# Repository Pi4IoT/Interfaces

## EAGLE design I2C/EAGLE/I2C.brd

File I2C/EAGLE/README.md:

<h3>EAGLE: Schematic & Board Layout</h3>

</br>

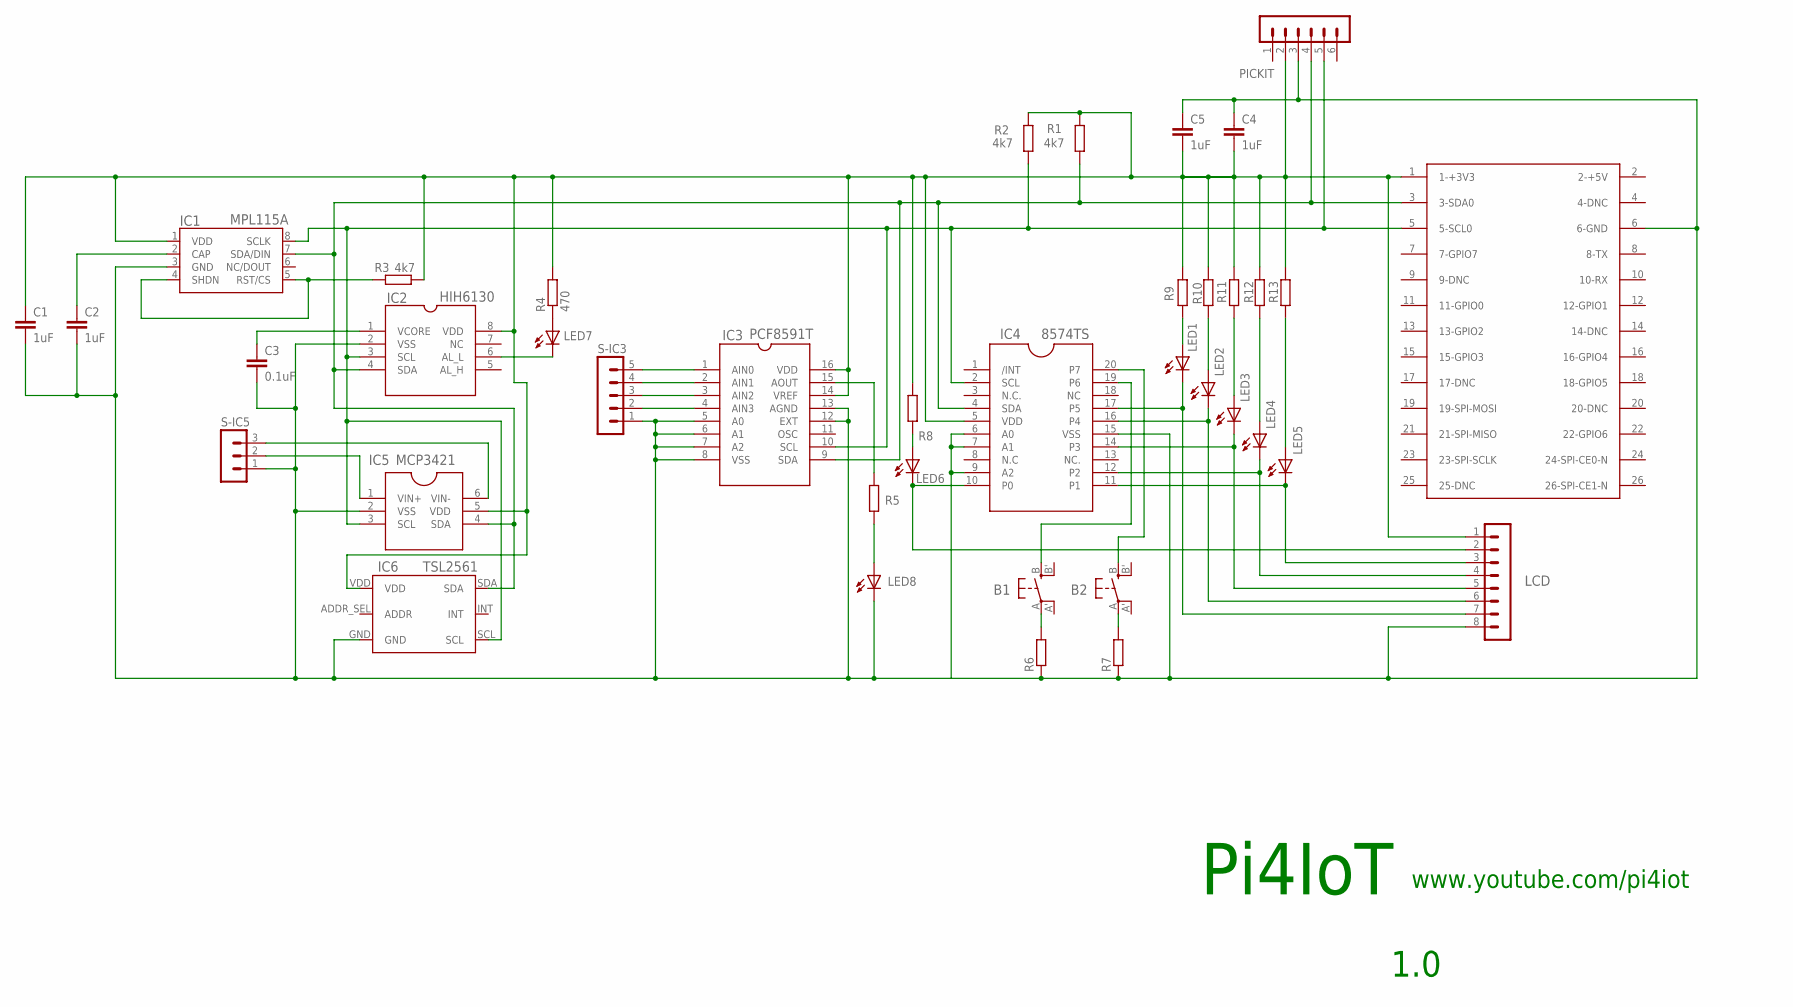
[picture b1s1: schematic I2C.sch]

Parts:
B1, B2: SWITCH_TACT_SMT; EVQ-Q2
C1, C2, C4, C5: 1uF; C1206
C3: 0.1uF; C1206
IC1: MPL115A; LGA8
IC2: HIH6130; SO08
IC3: PCF8591T; SO-16W
IC4: 8574TS; SSOP20
IC5: MCP3421; SOT23-6
IC6: TSL2561; TSL2561T
LCD: MA08-1
LED1, LED2, LED3, LED4, LED5, LED6, LED7, LED8: LEDSML0603; SML0603
PI: RASPBERRY-PI
PICKIT: MA06-1
R1, R2, R3: 4k7; R0603
R4: 470; R0603
R5, R6, R7, R8, R9, R10, R11, R12, R13: R-EU_R0603; R0603
S-IC3: MA05-1
S-IC5: MA03-1

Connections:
GND: C1.2, C2.2, C3.2, C4.1, C5.1, IC1.3 (GND), IC2.2 (VSS), IC3.5 (A0), IC3.6 (A1), IC3.7 (A2), IC3.8 (VSS), IC3.12 (EXT), IC3.13 (AGND), IC4.6 (A0), IC4.7 (A1), IC4.9 (A2), IC4.15 (VSS), IC5.2 (VSS), IC6.GND, LCD.8, LED8.C, PI.6 (6-GND), PICKIT.3, R6.1, R7.1, S-IC3.1, S-IC5.1
L1/4: IC4.16 (P4), LCD.6, LED2.C
LED4-4: IC4.12 (P2), LCD.4, LED4.C
unnamed: C3.1, IC2.1 (VCORE)
unnamed: C1.1, C4.2, C5.2, IC1.1 (VDD), IC2.8 (VDD), IC3.14 (VREF), IC3.16 (VDD), IC4.5 (VDD), IC5.5 (VDD), IC6.VDD, LCD.1, PI.1 (1-+3V3), PICKIT.2, R1.2, R2.2, R3.1, R4.2, R8.2, R9.2, R10.2, R11.2, R12.2, R13.2
unnamed: IC1.8 (SCLK), IC2.3 (SCL), IC3.10 (SCL), IC4.2 (SCL), IC5.3 (SCL), IC6.SCL, PI.5 (5-SCL0), PICKIT.5, R2.1
unnamed: C2.1, IC1.2 (CAP)
unnamed: IC1.7 (SDA/DIN), IC2.4 (SDA), IC3.9 (SDA), IC4.4 (SDA), IC5.4 (SDA), IC6.SDA, PI.3 (3-SDA0), PICKIT.4, R1.1
unnamed: IC1.4 (SHDN), IC1.5 (RST/CS), R3.2
unnamed: IC2.6 (AL_L), LED7.C
unnamed: LED7.A, R4.1
unnamed: IC3.15 (AOUT), R5.2
unnamed: LED8.A, R5.1
unnamed: IC3.4 (AIN3), S-IC3.2
unnamed: IC3.3 (AIN2), S-IC3.3
unnamed: IC3.2 (AIN1), S-IC3.4
unnamed: IC3.1 (AIN0), S-IC3.5
unnamed: IC5.6 (VIN-), S-IC5.3
unnamed: IC4.10 (P0), LCD.2, LED6.C
unnamed: IC5.1 (VIN+), S-IC5.2
unnamed: LED1.A, R9.1
unnamed: LED2.A, R10.1
unnamed: LED3.A, R11.1
unnamed: LED4.A, R12.1
unnamed: LED5.A, R13.1
unnamed: IC4.11 (P1), LCD.3, LED5.C
unnamed: LED6.A, R8.1
unnamed: IC4.14 (P3), LCD.5, LED3.C
unnamed: B1.B (S), IC4.19 (P6)
unnamed: IC4.17 (P5), LCD.7, LED1.C
unnamed: B2.B (S), IC4.20 (P7)
unnamed: B1.A, R6.2
unnamed: B2.A, R7.2

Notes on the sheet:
1.0
Pi4IoT
www.youtube.com/pi4iot

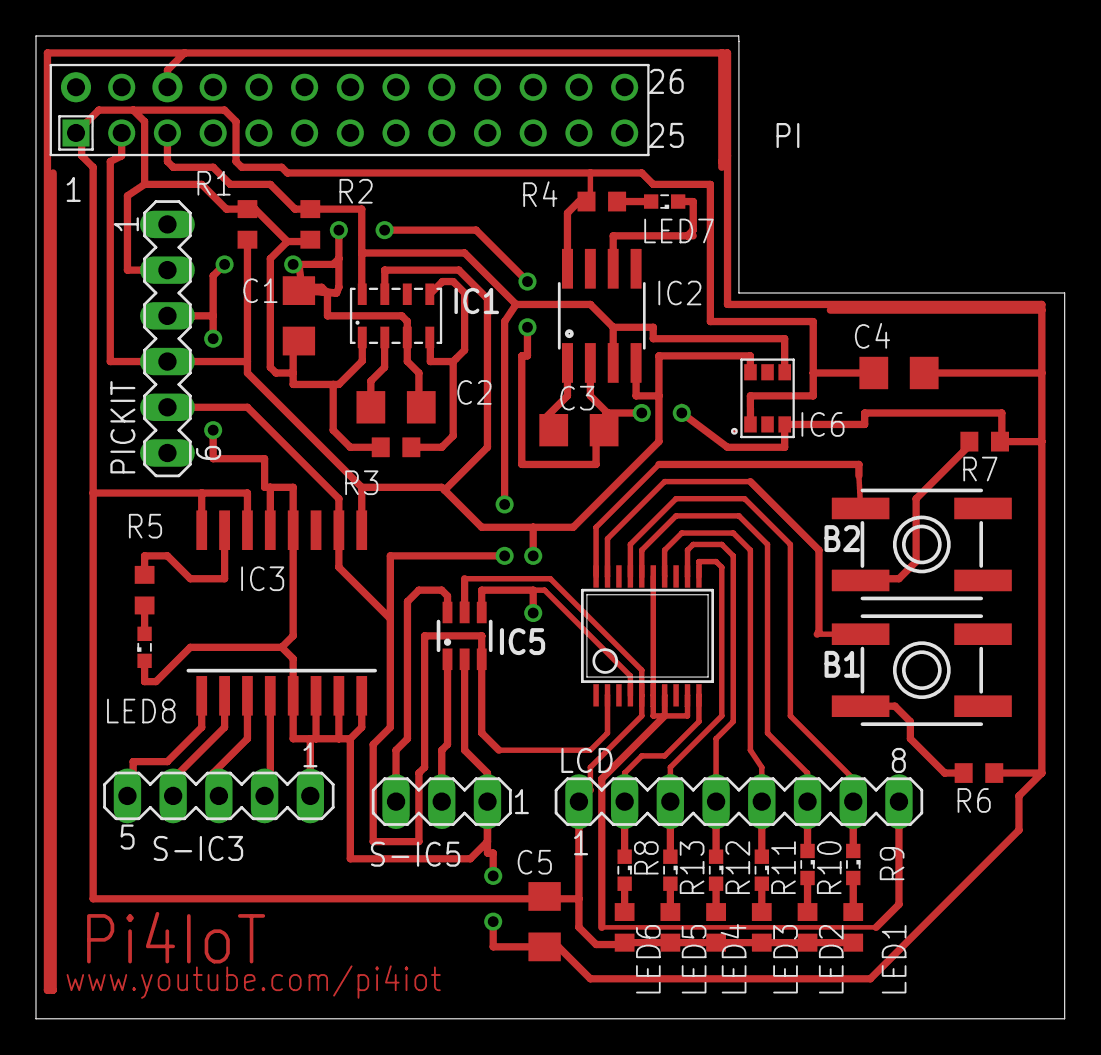
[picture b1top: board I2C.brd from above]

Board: 2 copper layers, 57.1 x 54.6 mm, 39 parts (0 on the bottom side), 33 nets.

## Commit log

2018-12-24 Create I2C
2018-12-24 Create README:md
2018-12-24 Update README:md
2019-02-20 Rename serial_bluetooth.c.txt to serial_bluetooth.ino

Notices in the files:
parts and their libraries:
SparkFun-Sensors: Licensing: CC v3.0 Share-Alike You are welcome to use this library for commercial purposes.
microbuilder: This work is placed in the public domain, and may be freely used for commercial and non-commercial work with the following conditions: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
